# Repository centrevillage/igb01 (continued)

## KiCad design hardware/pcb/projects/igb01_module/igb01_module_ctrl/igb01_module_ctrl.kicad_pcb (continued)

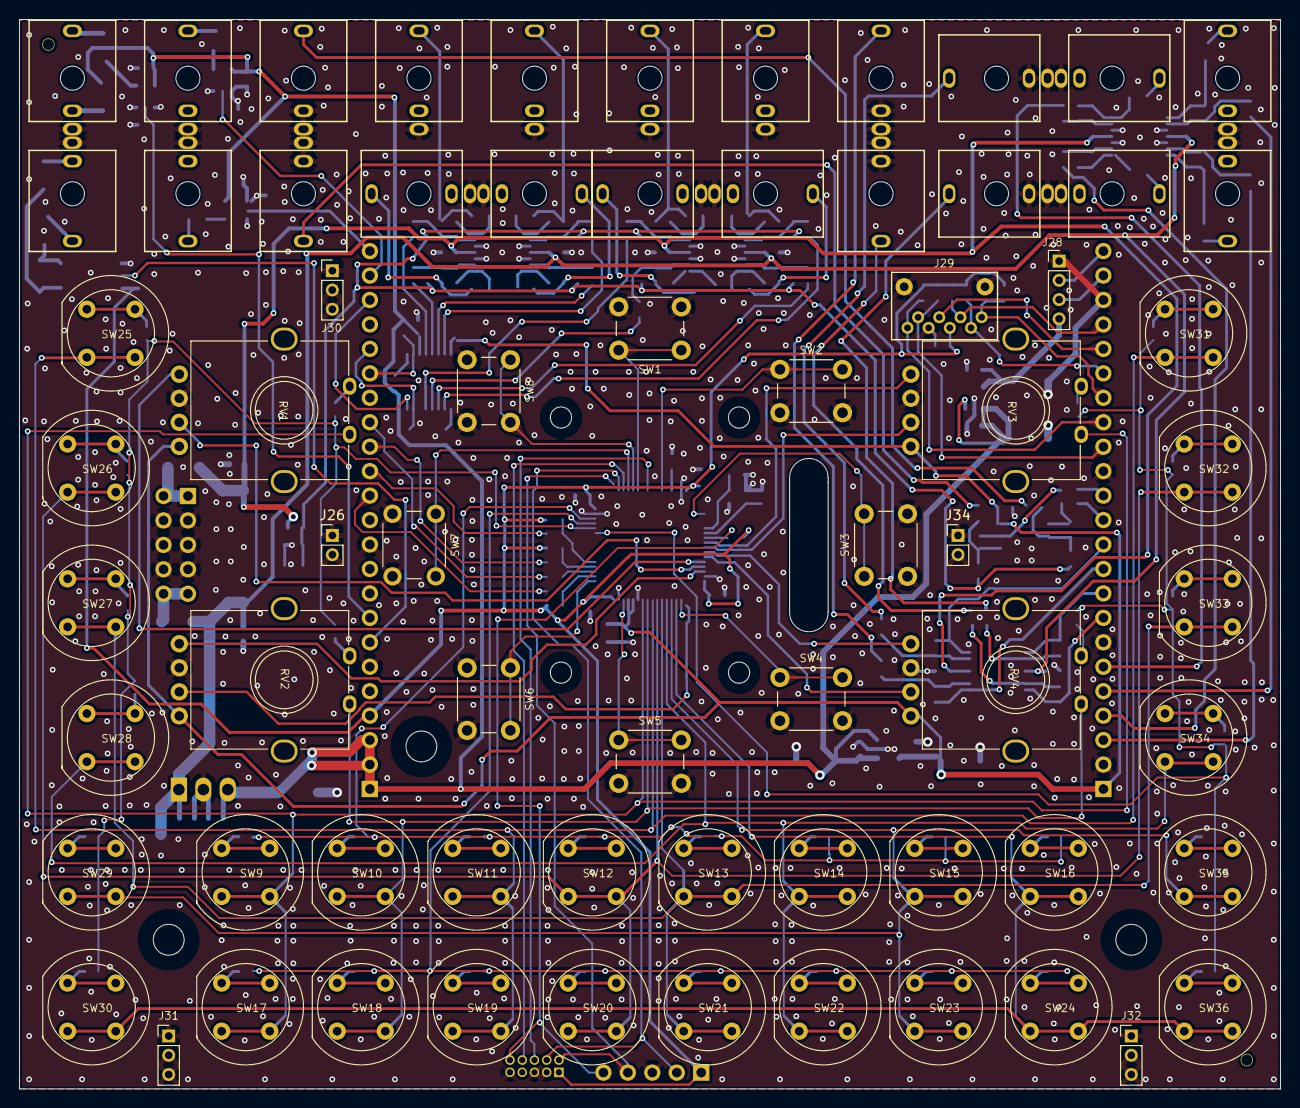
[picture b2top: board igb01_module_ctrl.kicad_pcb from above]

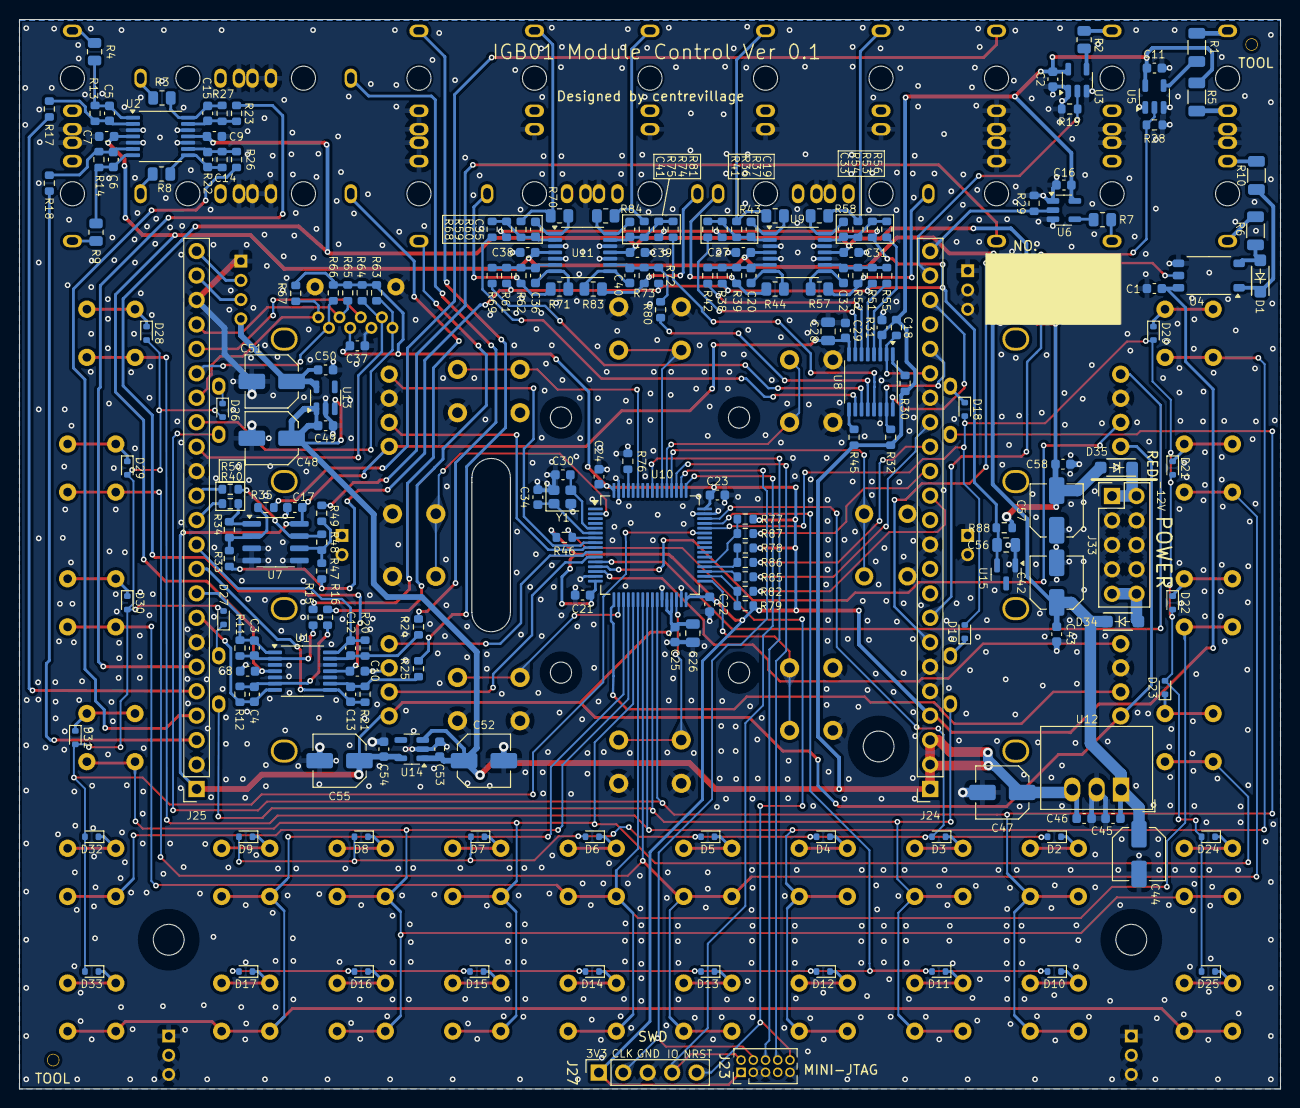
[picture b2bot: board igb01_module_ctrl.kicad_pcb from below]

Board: 2 copper layers, 131.0 x 111.1 mm, 278 parts (202 on the bottom side), 182 nets.

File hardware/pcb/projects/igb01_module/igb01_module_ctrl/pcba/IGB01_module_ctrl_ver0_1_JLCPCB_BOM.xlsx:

Comment | Designator | Footprint | LCSC Part #（optional）
220Ω,1206 | R1,R6,R5,R10 | R1206 | C17957
10kΩ,0603 | R20,R76,R77,R28,R19,R27,R12,R11,R21,R17,R46,R79,R78,R26,R29,R18 | R0603 | C25804
100kΩ,0603 | R24,R14,R16,R22,R23,R15,R25,R13 | R0603 | C25803
47Ω,0603 | R40,R50 | R0603 | C23182
200kΩ,0603 | R61,R72,R53,R49,R62,R54,R51,R59,R52,R33,R75,R36,R39,R37,R38,R74,R35,R73,R60,R47 | R0603 | C25811
47kΩ,0603 | R66,R63,R45,R32,R65,R31,R30,R67,R64 | R0603 | C25819
33kΩ,0603 | R69,R81,R80,R68,R34,R48,R56,R55,R41,R42 | R0603 | C4216
1kΩ,0805 | R70,R58,R4,R8,R84,R9,R43,R44,R2,R71,R83,R57,R7,R3 | R0805 | C17513
22Ω,0603 | R85,R82,R87,R86 | R0603 | C23345
3.3kΩ,0603 | R88 | R0603 | C22978
100nF,0603 | C11,C39,C53,C7,C1,C50,C38,C25,C23,C37,C54,C8,C29,C58,C49,C10,C24,C45,C17,C9,C27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 | R0603 | C14663
10pF,0603 | C14,C15,C5,C6 | R0603 | C1634
18pF,0603 | C20,C34,C3,C30,C33,C4,C19,C41,C13,C35,C12,C32,C40,C36 | R0603 | C1647
10uF,0805 | C26,C28 | C0805 | C15850
100uF,D5 | C51 | C_Elec_5x5.8 | C3347
1uF,0805 | C56 | C0805 | C28323
47uF,D5 | C57,C47,C55,C48,C44,C52,C42 | C_Elec_5x5.8 | C3337
1N4148,SOD-123 | D1 | SOD-123 | C81598
1N4148,SOD-523 | D23,D13,D8,D2,D14,D28,D16,D31,D6,D20,D15,D22,D5,D9,D29,D32,D25,D3,D24,D19,D30,D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 | SOD-523 | C27748
DSK34,SOD-123 | D35,D34 | SOD-123 | C41029
STM32G431RBT6 | U10 | LQFP-64_10x10mm_P0.5mm | C431633
TL074HIPWR,TSSOP | U11,U2,U1,U9 | TSSOP-14_4.4x5mm_P0.65mm | C4370424
R-78B5.0-2.0 | U12 | Converter_DCDC_RECOM_R-78B-2.0_THT | C5199920
LDK320-3.3V,SOT-23-5 | U14,U13 | SOT-23-5 | C136155
LM4040DBZ-10,SOT-23 | U15 | SOT-23 | C129969
TLP2361 | U4 | SO-5-6_4.55x3.7mm_P1.27mm | C107626
74AHCT1G125,SOT-23-5 | U5,U6,U3 | SOT-23-5 | C7484
MCP6002,SOIC | U7 | SOIC-8_3.9x4.9mm_P1.27mm | C7377
DAC8568IBPW,TSSOP | U8 | TSSOP-16_4.4x5mm_P0.65mm | C2680013
Crystal, 12MHz | Y1 | Crystal_SMD_2520-4Pin_2.5x2.0mm | C284156
Pin Header, 2x5, P1.27mm | J23 | PinHeader_2x05_P1.27mm_Vertical
Pin Socket, 1x23, P2.54mm | J24 | PinSocket_1x23_P2.54mm_Vertical
Pin Socket, 1x23, P2.54mm | J25 | PinSocket_1x23_P2.54mm_Vertical
Pin Socket, 1x5, P2.54mm | J27 | PinSocket_1x05_P2.54mm_Vertical
Pin Header, 2x5, P2.54mm | J33 | PinHeader_2x05_P2.54mm_Vertical

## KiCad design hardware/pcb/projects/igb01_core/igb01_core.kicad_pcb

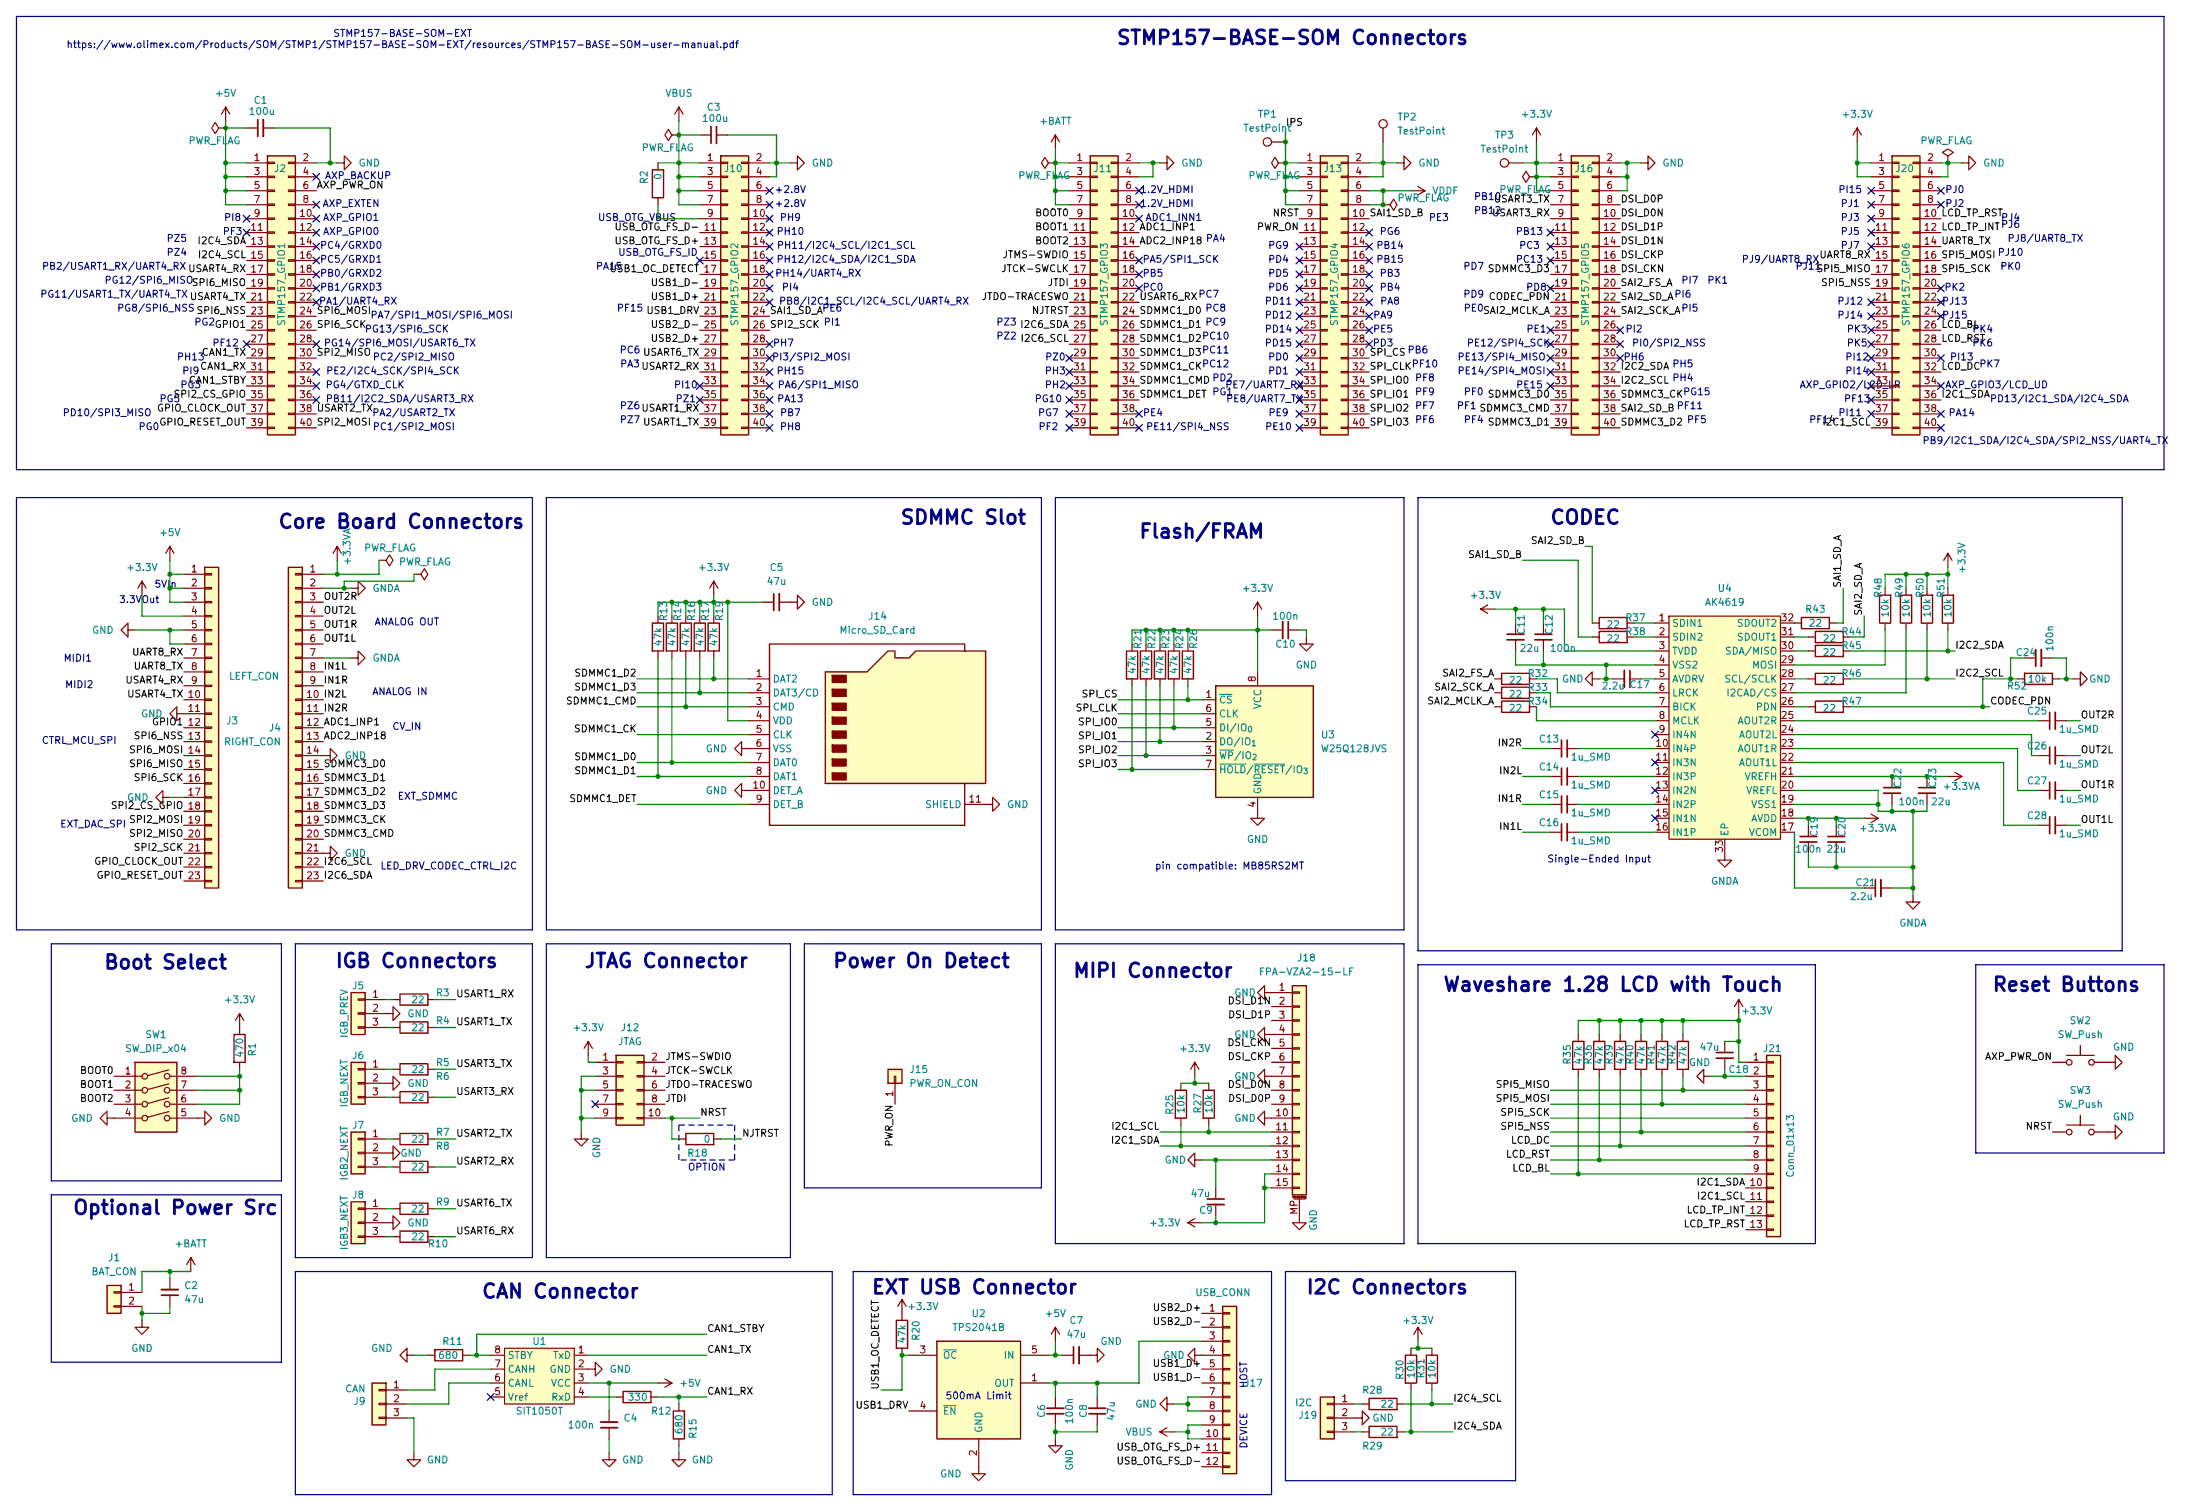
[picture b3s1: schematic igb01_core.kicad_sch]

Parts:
C1, C3: 100u; C_1206_3216Metric
C2, C5, C7, C8, C9, C18: 47u; C_0805_2012Metric
C4, C6, C10, C12, C19, C22, C24: 100n; C_0402_1005Metric
C11, C20, C23: 22u; C_0805_2012Metric
C13, C14, C15, C16, C25, C26, C27, C28: 1u_SMD; C_0805_2012Metric
C17, C21: 2.2u; C_0603_1608Metric
J1: BAT_CON; Molex_KK-254_AE-6410-02A_1x02_P2.54mm_Vertical
J2: STMP157_GPIO1; PinHeader_2x20_P1.27mm_Vertical_SMD
J3: LEFT_CON; PinHeader_1x23_P2.54mm_Vertical
J4: RIGHT_CON; PinHeader_1x23_P2.54mm_Vertical
J5: IGB_PREV; Molex_KK-254_AE-6410-03A_1x03_P2.54mm_Vertical
J6: IGB_NEXT; Molex_KK-254_AE-6410-03A_1x03_P2.54mm_Vertical
J7: IGB2_NEXT; Molex_KK-254_AE-6410-03A_1x03_P2.54mm_Vertical
J8: IGB3_NEXT; Molex_KK-254_AE-6410-03A_1x03_P2.54mm_Vertical
J9: CAN; Molex_KK-254_AE-6410-03A_1x03_P2.54mm_Vertical
J10: STMP157_GPIO2; PinHeader_2x20_P1.27mm_Vertical_SMD
J11: STMP157_GPIO3; PinHeader_2x20_P1.27mm_Vertical_SMD
J12: JTAG; PinHeader_2x05_P1.27mm_Vertical_SMD
J13: STMP157_GPIO4; PinHeader_2x20_P1.27mm_Vertical_SMD
J14: Micro_SD_Card; Molex_uSD_1040310811
J15: PWR_ON_CON; PinHeader_1x01_P2.54mm_Vertical
J16: STMP157_GPIO5; PinHeader_2x20_P1.27mm_Vertical_SMD
J17: USB_CONN; Molex_KK-254_AE-6410-12A_1x12_P2.54mm_Vertical
J18: FPA-VZA2-15-LF; Molex_200528-0150_1x15-1MP_P1.00mm_Horizontal
J19: I2C; Molex_KK-254_AE-6410-03A_1x03_P2.54mm_Vertical
J20: STMP157_GPIO6; PinHeader_2x20_P1.27mm_Vertical_SMD
J21: Conn_01x13; PinHeader_1x13_P2.54mm_Horizontal
R1: 470; R_0603_1608Metric
R2, R18: 0; R_0603_1608Metric
R3, R4, R5, R6, R7, R8, R9, R10, R28, R29: 22; R_0603_1608Metric
R11, R15: 680; R_0603_1608Metric
R12: 330; R_0603_1608Metric
R13, R14, R16, R17, R19, R20, R21, R22, R23, R24, R26, R35, R36, R39, R40, R41, R42: 47k; R_0402_1005Metric
R25, R27, R30, R31, R48, R49, R50, R51: 10k; R_0402_1005Metric
R32, R33, R34, R37, R38, R43, R44, R45, R46, R47: 22; R_0402_1005Metric
R52: 10k; R_0603_1608Metric
SW1: SW_DIP_x04; DIP_Switch_1.27mm_SMD
SW2, SW3: SW_Push; SW_SPST_PTS647_Sx38
TP1, TP2, TP3: TestPoint; PinHeader_1x01_P2.54mm_Vertical
U1: SIT1050T; SOP-8_3.9x4.9mm_P1.27mm
U2: TPS2041B; SOT-23-5
U3: W25Q128JVS; SOIC-8_5.3x5.3mm_P1.27mm
U4: AK4619; QFN-32-1EP_5x5mm_P0.5mm_EP3.6x3.6mm

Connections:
+3.3V: C5.1, C9.2, C10.2, C11.1, C12.1, C18.1, J3.4, J12.1, J14.4 (VDD), J16.1, J16.3, J16.5, J18.14, J18.15, J20.1, J20.3, J21.1, R1.1, R13.1, R14.1, R16.1, R17.1, R19.1, R20.1, R21.1, R22.1, R23.1, R24.1, R25.1, R26.1, R27.1, R30.1, R31.1, R35.1, R36.1, R39.1, R40.1, R41.1, R42.1, R48.2, R49.2, R50.2, R51.2, TP3.1, U3.8 (VCC), U4.3 (TVDD)
+3.3VA: C19.1, C20.1, C22.1, C23.1, J4.1, U4.18 (AVDD), U4.21 (VREFH)
+5V: C1.1, C4.2, C7.1, J2.1, J2.3, J2.5, J2.7, J3.1, J3.2, J3.3, U1.3 (VCC), U2.5 (IN)
+BATT: C2.2, J1.1, J11.1, J11.3, J11.5, J11.7
/ SAI1_SD_B: J13.10, R38.1
/ADC1_INP1: J4.12, J11.12
/ADC2_INP18: J4.13, J11.14
/AXP_PWR_ON: J2.6, SW2.1
/BOOT0: J11.9, SW1.1
/BOOT1: J11.11, SW1.2
/BOOT2: J11.13, SW1.3
/CAN1_RX: J2.31, R12.2, R15.2
/CAN1_STBY: J2.33, R11.1, U1.8 (STBY)
/CAN1_TX: J2.29, U1.1 (TxD)
/CODEC_PDN: C24.1, J16.21, R47.2, R52.2
/DSI_CKN: J16.18, J18.5
/DSI_CKP: J16.16, J18.6
/DSI_D0N: J16.10, J18.8
/DSI_D0P: J16.8, J18.9
/DSI_D1N: J16.14, J18.2
/DSI_D1P: J16.12, J18.3
/GPIO1: J2.25, J3.12
/GPIO_CLOCK_OUT: J2.37, J3.22
/GPIO_RESET_OUT: J2.39, J3.23
/I2C1_SCL: J18.11, J20.39, J21.11, R27.2
/I2C1_SDA: J18.12, J20.36, J21.10, R25.2
/I2C2_SCL: J16.34, R46.2, R50.1
/I2C2_SDA: J16.32, R45.2, R51.1
/I2C4_SCL: J2.15, R28.2, R31.2
/I2C4_SDA: J2.13, R29.2, R30.2
/I2C6_SCL: J4.22, J11.27
/I2C6_SDA: J4.23, J11.25
/IN1L: C16.1, J4.8
/IN1R: C15.1, J4.9
/IN2L: C14.1, J4.10
/IN2R: C13.1, J4.11
/IPS: J13.1, J13.3, J13.5, J13.7, TP1.1
/JTCK-SWCLK: J11.17, J12.4
/JTDI: J11.19, J12.8
/JTDO-TRACESWO: J11.21, J12.6
/JTMS-SWDIO: J11.15, J12.2
/LCD_BL: J20.26, J21.9, R35.2
/LCD_DC: J20.32, J21.7, R39.2
/LCD_RST: J20.28, J21.8, R36.2
/LCD_TP_INT: J20.12, J21.12
/LCD_TP_RST: J20.10, J21.13
/NJTRST: J11.23, R18.2
/NRST: J12.10, J13.9, R18.1, SW3.1
/OUT1L: C28.2, J4.6
/OUT1R: C27.2, J4.5
/OUT2L: C26.2, J4.4
/OUT2R: C25.2, J4.3
/PWR_ON: J13.11, J15.1
/SAI1_SD_A: J10.24, R43.2
/SAI2_FS_A: J16.20, R32.1
/SAI2_MCLK_A: J16.23, R34.1
/SAI2_SCK_A: J16.24, R33.1
/SAI2_SD_A: J16.22, R44.2
/SAI2_SD_B: J16.38, R37.1
/SDMMC1_CK: J11.32, J14.5 (CLK)
/SDMMC1_CMD: J11.34, J14.3 (CMD), R16.2
/SDMMC1_D0: J11.24, J14.7 (DAT0), R14.2
/SDMMC1_D1: J11.26, J14.8 (DAT1), R13.2
/SDMMC1_D2: J11.28, J14.1 (DAT2), R19.2
/SDMMC1_D3: J11.30, J14.2 (DAT3/CD), R17.2
/SDMMC1_DET: J11.36, J14.9 (DET_B)
/SDMMC3_CK: J4.19, J16.36
/SDMMC3_CMD: J4.20, J16.37
/SDMMC3_D0: J4.15, J16.35
/SDMMC3_D1: J4.16, J16.39
/SDMMC3_D2: J4.17, J16.40
/SDMMC3_D3: J4.18, J16.17
/SPI2_CS_GPIO: J2.35, J3.18
/SPI2_MISO: J2.30, J3.20
/SPI2_MOSI: J2.40, J3.19
/SPI2_SCK: J3.21, J10.26
/SPI5_MISO: J20.17, J21.3, R42.2
/SPI5_MOSI: J20.16, J21.4, R41.2
/SPI5_NSS: J20.19, J21.6, R40.2
/SPI5_SCK: J20.18, J21.5
/SPI6_MISO: J2.19, J3.15
/SPI6_MOSI: J2.24, J3.14
/SPI6_NSS: J2.23, J3.13
/SPI6_SCK: J2.26, J3.16
/SPI_CLK: J13.32, U3.6 (CLK)
/SPI_CS: J13.30, R26.2, U3.1 (~CS)
/SPI_IO0: J13.34, R24.2, U3.5 (DI/IO_{0})
/SPI_IO1: J13.36, R23.2, U3.2 (DO/IO_{1})
/SPI_IO2: J13.38, R22.2, U3.3 (~WP/IO_{2})
/SPI_IO3: J13.40, R21.2, U3.7 (~HOLD/~RESET/IO_{3})
/UART8_RX: J3.7, J20.15
/UART8_TX: J3.8, J20.14
/USART1_RX: J10.37, R3.2
/USART1_TX: J10.39, R4.2
/USART2_RX: J10.31, R8.2
/USART2_TX: J2.38, R7.2
/USART3_RX: J16.9, R6.2
/USART3_TX: J16.7, R5.2
/USART4_RX: J2.17, J3.9
/USART4_TX: J2.21, J3.10
/USART6_RX: J11.22, R10.2
/USART6_TX: J10.29, R9.2
/USB1_D+: J10.21, J17.5
/USB1_D-: J10.19, J17.6
/USB1_DRV: J10.23, U2.4 (~EN)
/USB1_OC_DETECT: J10.17, R20.2, U2.3 (~OC)
/USB2_D+: J10.27, J17.1
/USB2_D-: J10.25, J17.2
/USB_OTG_FS_D+: J10.13, J17.11
/USB_OTG_FS_D-: J10.11, J17.12
GND: C1.2, C2.1, C3.2, C4.1, C5.2, C6.1, C7.2, C8.1, C9.1, C10.1, C11.2, C12.2, C17.2, C18.2, C24.2, J1.2, J2.2, J3.5, J3.6, J3.11, J3.17, J4.14, J4.21, J5.2, J6.2, J7.2, J8.2, J9.3, J10.2, J10.4, J11.2, J11.4, J12.3, J12.5, J12.9, J13.2, J13.4, J14.6 (VSS), J14.10 (DET_A), J14.11 (SHIELD), J16.2, J16.4, J16.6, J17.4, J17.7, J17.8, J18.1, J18.4, J18.7, J18.10, J18.13, J18.MP (MountPin), J19.2, J20.2, J20.4, J21.2, R11.2, R15.1, R52.1, SW1.4, SW1.5, SW2.2, SW3.2, TP2.1, U1.2 (GND), U2.2 (GND), U3.4 (GND), U4.4 (VSS2)
GNDA: C19.2, C20.2, C21.2, C22.2, C23.2, J4.2, J4.7, U4.19 (VSS1), U4.20 (VREFL), U4.33 (EP)
unnamed: J5.1, R3.1
unnamed: J5.3, R4.1
unnamed: J6.1, R5.1
unnamed: J6.3, R6.1
unnamed: J7.1, R7.1
unnamed: J7.3, R8.1
unnamed: J8.1, R9.1
unnamed: J8.3, R10.1
unnamed: J9.1, U1.7 (CANH)
unnamed: J9.2, U1.6 (CANL)
unnamed: J10.9, R2.1
unnamed: C6.2, C8.2, J17.3, U2.1 (OUT)
unnamed: J19.1, R28.1
unnamed: J19.3, R29.1
unnamed: R1.2, SW1.6, SW1.7, SW1.8
unnamed: R12.1, U1.4 (RxD)
unnamed: C28.1, U4.22 (AOUT1L)
unnamed: C27.1, U4.23 (AOUT1R)
unnamed: C26.1, U4.24 (AOUT2L)
unnamed: C25.1, U4.25 (AOUT2R)
unnamed: C17.1, U4.5 (AVDRV)
unnamed: R33.2, U4.7 (BICK)
unnamed: R49.1, U4.27 (I2CAD/CS)
unnamed: C16.2, U4.16 (IN1P)
unnamed: C15.2, U4.14 (IN2P)
unnamed: C14.2, U4.12 (IN3P)
unnamed: C13.2, U4.10 (IN4P)
unnamed: R32.2, U4.6 (LRCK)
unnamed: R34.2, U4.8 (MCLK)
unnamed: R48.1, U4.29 (MOSI)
unnamed: R47.1, U4.26 (PDN)
unnamed: R46.1, U4.28 (SCL/SCLK)
unnamed: R45.1, U4.30 (SDA/MISO)
unnamed: R37.2, U4.1 (SDIN1)
unnamed: R38.2, U4.2 (SDIN2)
unnamed: R44.1, U4.31 (SDOUT1)
unnamed: R43.1, U4.32 (SDOUT2)
unnamed: C21.1, U4.17 (VCOM)
VBUS: C3.1, J10.1, J10.3, J10.5, J10.7, J17.9, J17.10, R2.2
VDDF: J13.6, J13.8

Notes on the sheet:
PG4/GTXD_CLK
PD7
STMP157-BASE-SOM-EXT https://www.olimex.com/Products/SOM/STMP1/STMP157-BASE-SOM-EXT/resources/STMP157-BASE-SOM-user-manual.pdf
PF15
PK5
PH14/UART4_RX
PB14
PG8/SPI6_NSS
PD4
PE1
PZ4
PD8
PF10
PK4
PA14
PE5
PI11
Single-Ended Input
PC3
PE10
Boot Select
PK3
PI12
3.3VOut
PF2
Reset Buttons
PH5
PG2
CV_IN
PB11/I2C2_SDA/USART3_RX
PJ3
JTAG Connector
+2.8V
PG9
PH13
500mA Limit
Optional Power Src
PI6
PD14
LED_DRV_CODEC_CTRL_I2C

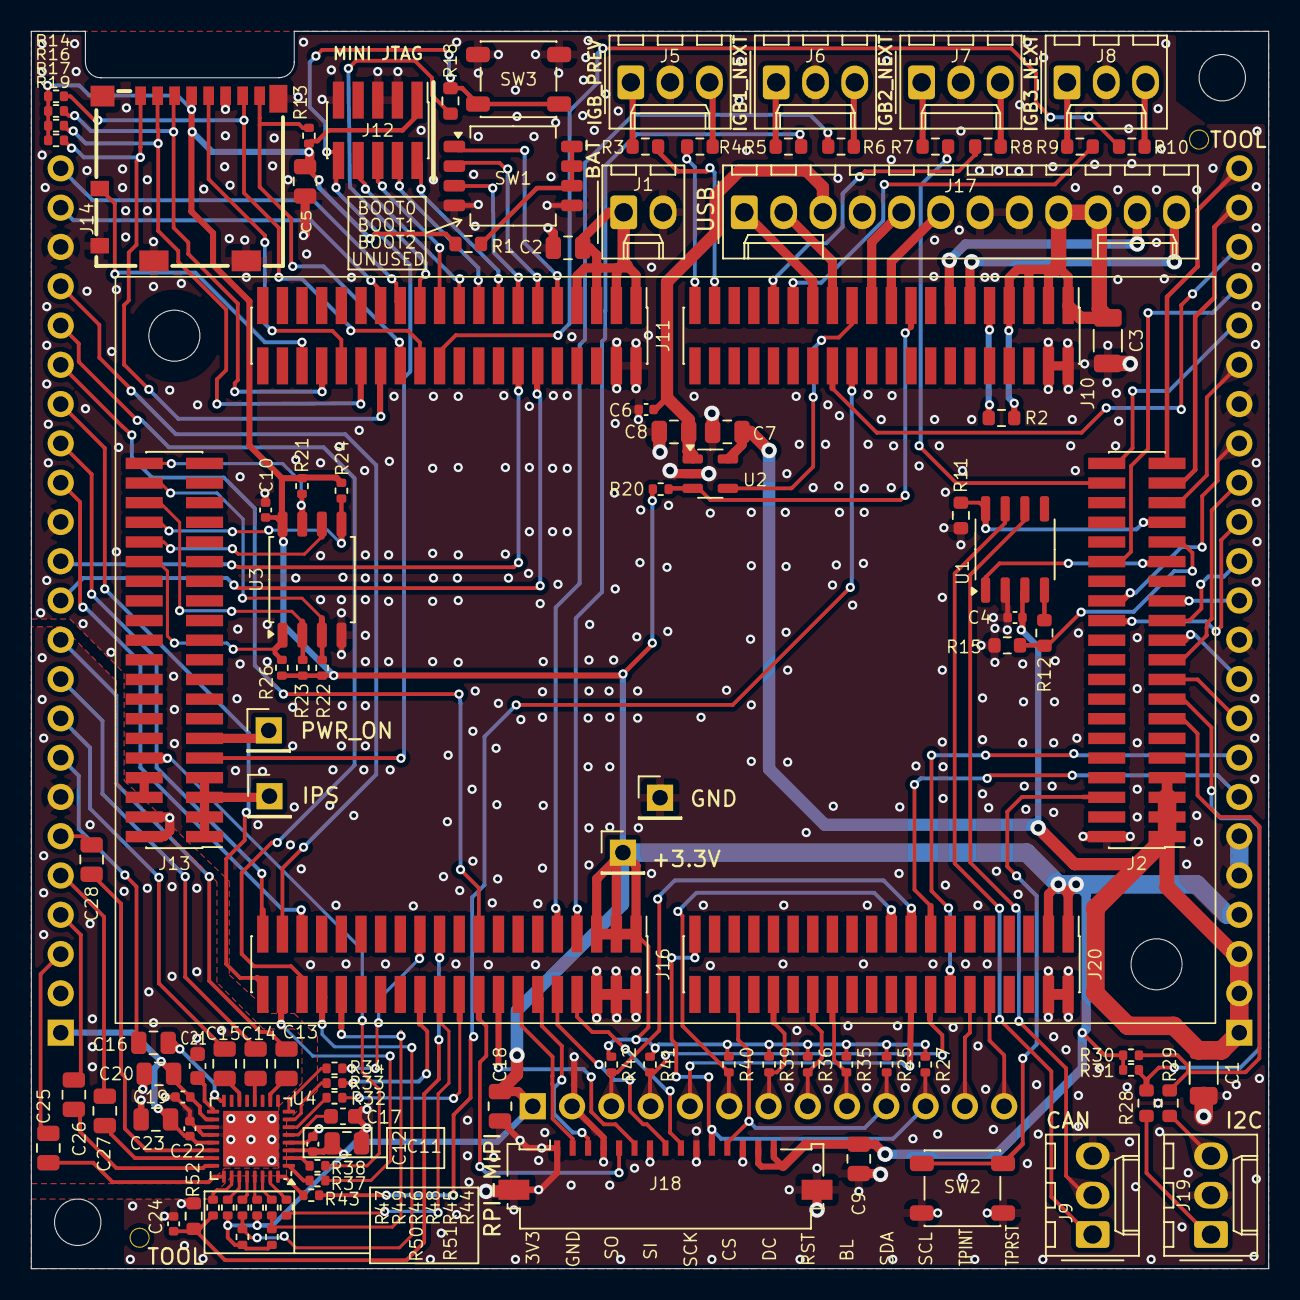
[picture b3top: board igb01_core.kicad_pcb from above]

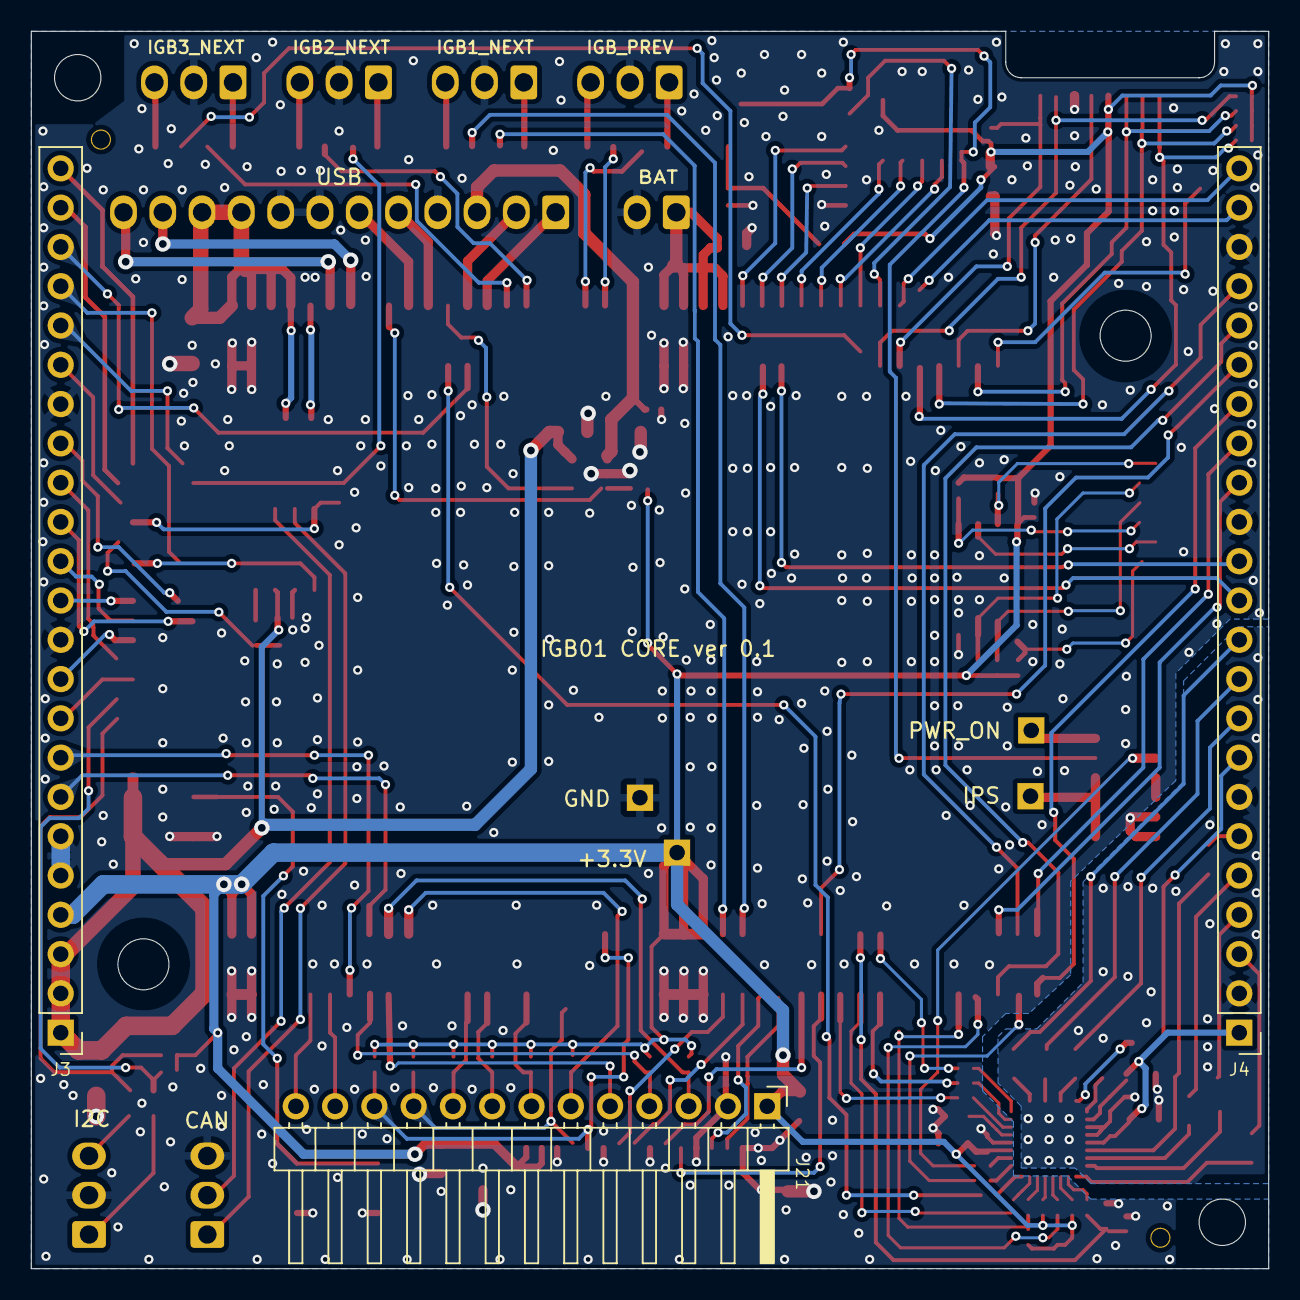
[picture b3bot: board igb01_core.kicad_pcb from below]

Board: 2 copper layers, 80.0 x 80.0 mm, 111 parts (3 on the bottom side), 152 nets.

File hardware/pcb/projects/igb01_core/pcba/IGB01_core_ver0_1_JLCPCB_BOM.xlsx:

Comment | Designator | Footprint | LCSC Part #（optional）
22uF | C11,C23,C20 | C0805 | C45783
2.2uF | C17,C21 | C0603 | C23630
1uF | C25,C14,C27,C15,C28,C16,C13,C26 | C0805 | C1712
100uF | C3,C1 | C1206 | C15008
100nF | C4,C10,C12,C22,C24,C19,C6 | C0402 | C1525
47uF | C8,C9,C5,C2,C7,C18 | C0805 | C16780
470Ω | R1 | R0603 | C23179
680Ω | R11,R15 | R0603 | C23228
330Ω | R12 | R0603 | C23138
0Ω | R2,R18 | R0603 | C21189
22Ω | R32,R44,R47,R34,R37,R45,R43,R33,R38,R46 | R0402 | C25092
47kΩ | R39,R20,R16,R36,R17,R14,R40,R23,R22,R21,R13,R35,R42,R19,R24,R41,R26 | R0402 | C25792
22Ω | R5,R6,R10,R28,R4,R3,R29,R9,R8,R7 | R0603 | C23345
10kΩ | R50,R51,R48,R31,R49,R30,R25,R27 | R0402 | C25744
10kΩ | R52 | R0603 | C25804
SIT1050T | U1 | SOP-8_3.9x4.9mm_P1.27mm | C313021
TPS2041B | U2 | SOT-23-5 | C51386
W25Q128JVS | U3 | SOIC-8_5.3x5.3mm_P1.27mm | C97521
AK4619 | U4 | QFN-32-1EP_5x5mm_P0.5mm_EP3.6x3.6mm | C3034747
DIP Switch, SMD | SW1 | DIP_Switch_1.27mm_SMD | C40736
Push Switch | SW3,SW2 | SW_SPST_PTS647_Sx38 | C2689502
Molex KK-254, 2 pin | J1 | Molex_KK-254_AE-6410-02A_1x02_P2.54mm_Vertical
Pin Header 2x20,pitch1.27mm,SMD | J10 | PinHeader_2x20_P1.27mm_Vertical_SMD | C2881925
Pin Header 2x20,pitch1.27mm,SMD | J11 | PinHeader_2x20_P1.27mm_Vertical_SMD | C2881925
Pin Header 2x05,pitch1.27mm,SMD | J12 | PinHeader_2x05_P1.27mm_Vertical_SMD | C41376037
Pin Header 2x20,pitch1.27mm,SMD | J13 | PinHeader_2x20_P1.27mm_Vertical_SMD | C2881925
Molex uSD 1040310811 | J14 | Molex_uSD_1040310811 | C585350
Pin Header 2x20,pitch1.27mm,SMD | J16 | PinHeader_2x20_P1.27mm_Vertical_SMD | C2881925
Molex KK-254, 12 pin | J17 | Molex_KK-254_AE-6410-12A_1x12_P2.54mm_Vertical
Molex 200528-0150 | J18 | Molex_200528-0150_1x15-1MP_P1.00mm_Horizontal | C6050043
Molex KK-254, 3 pin | J19 | Molex_KK-254_AE-6410-03A_1x03_P2.54mm_Vertical
Pin Header 2x20,pitch1.27mm,SMD | J2 | PinHeader_2x20_P1.27mm_Vertical_SMD | C2881925
Pin Header 2x20,pitch1.27mm,SMD | J20 | PinHeader_2x20_P1.27mm_Vertical_SMD | C2881925
Pin Header 1x13,pitch2.54mm,horizontal | J21 | PinHeader_1x13_P2.54mm_Horizontal
Pin Header 1x23,pitch2.54mm,vertical | J3 | PinHeader_1x23_P2.54mm_Vertical
Pin Header 1x23,pitch2.54mm,vertical | J4 | PinHeader_1x23_P2.54mm_Vertical
Molex KK-254, 3 pin | J5 | Molex_KK-254_AE-6410-03A_1x03_P2.54mm_Vertical
Molex KK-254, 3 pin | J6 | Molex_KK-254_AE-6410-03A_1x03_P2.54mm_Vertical
Molex KK-254, 3 pin | J7 | Molex_KK-254_AE-6410-03A_1x03_P2.54mm_Vertical
Molex KK-254, 3 pin | J8 | Molex_KK-254_AE-6410-03A_1x03_P2.54mm_Vertical
Molex KK-254, 3 pin | J9 | Molex_KK-254_AE-6410-03A_1x03_P2.54mm_Vertical

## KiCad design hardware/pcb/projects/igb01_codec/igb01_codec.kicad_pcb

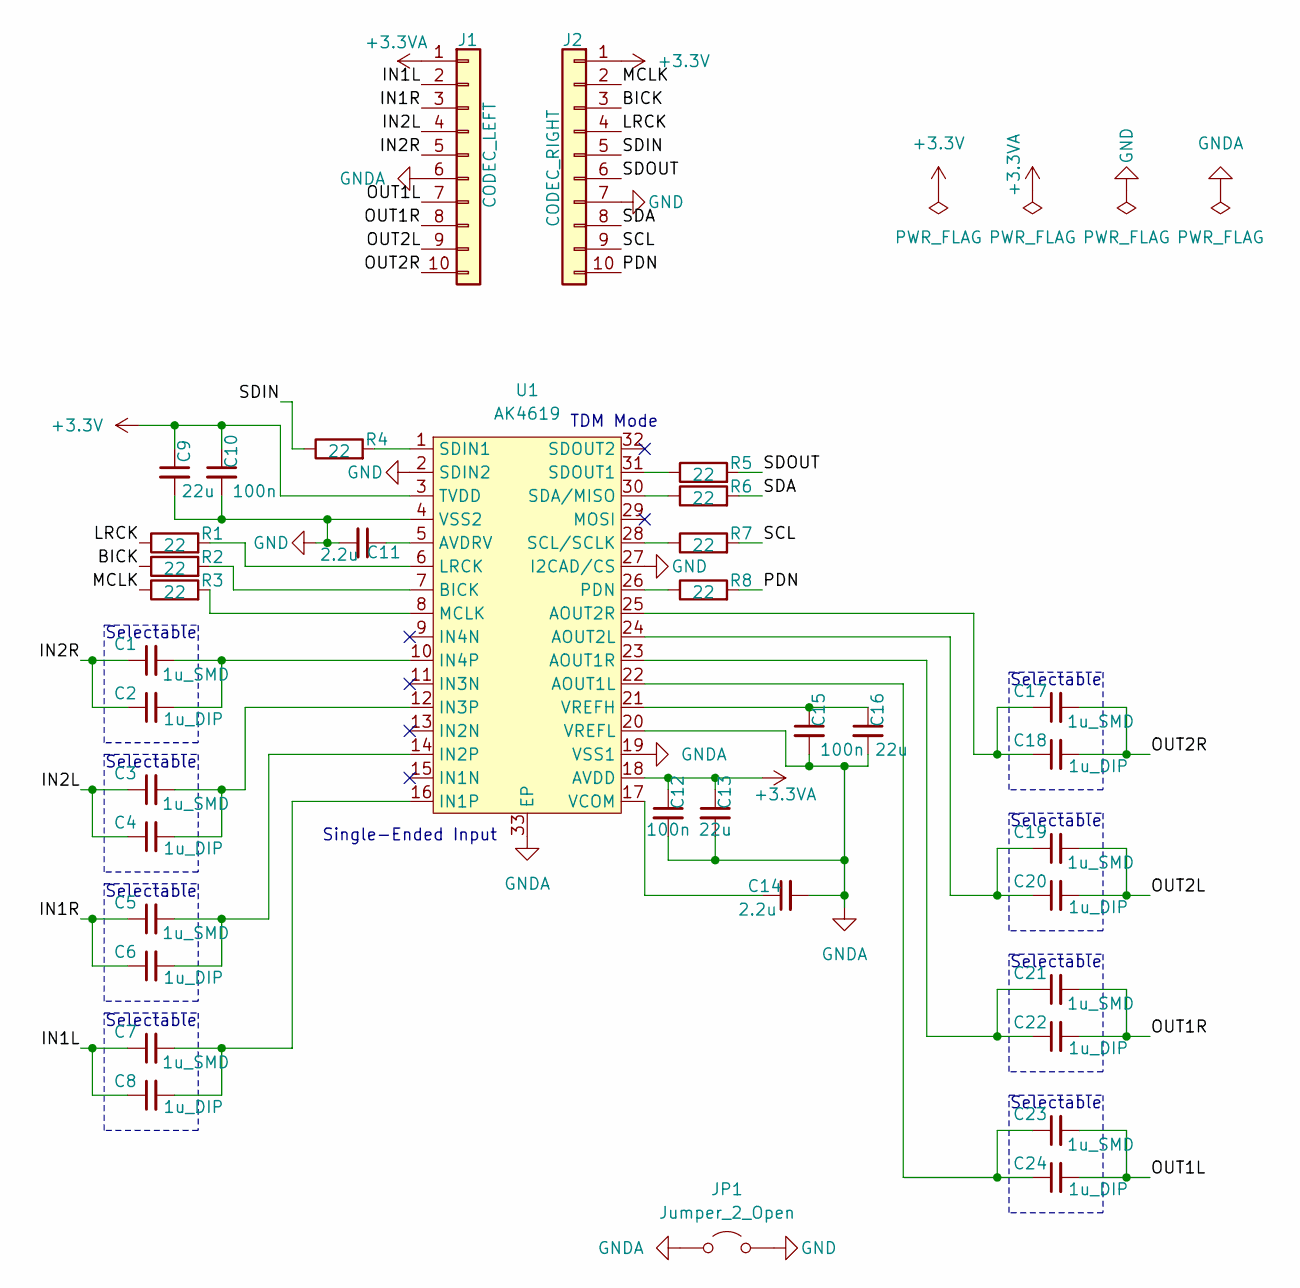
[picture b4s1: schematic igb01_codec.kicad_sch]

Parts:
C1, C3, C5, C7, C17, C19, C21, C23: 1u_SMD; C_1206_3216Metric
C2, C4, C6, C8, C18, C20, C22, C24: 1u_DIP; C_Rect_L7.2mm_W4.5mm_P5.00mm_FKS2_FKP2_MKS2_MKP2
C9, C13, C16: 22u; C_0805_2012Metric
C10, C12, C15: 100n; C_0402_1005Metric
C11, C14: 2.2u; C_0603_1608Metric
J1: CODEC_LEFT; PinHeader_1x10_P2.54mm_Vertical
J2: CODEC_RIGHT; PinHeader_1x10_P2.54mm_Vertical
JP1: Jumper_2_Open; SolderJumper-2_P1.3mm_Open_RoundedPad1.0x1.5mm
R1, R2, R3, R4, R5, R6, R7, R8: 22; R_0402_1005Metric
U1: AK4619; QFN-32-1EP_5x5mm_P0.5mm_EP3.6x3.6mm

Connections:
+3.3V: C9.1, C10.1, J2.1, U1.3 (TVDD)
+3.3VA: C12.1, C13.1, J1.1, U1.18 (AVDD)
/BICK: J2.3, R2.1
/IN1L: C7.1, C8.1, J1.2
/IN1R: C5.1, C6.1, J1.3
/IN2L: C3.1, C4.1, J1.4
/IN2R: C1.1, C2.1, J1.5
/LRCK: J2.4, R1.1
/MCLK: J2.2, R3.1
/OUT1L: C23.2, C24.2, J1.7
/OUT1R: C21.2, C22.2, J1.8
/OUT2L: C19.2, C20.2, J1.9
/OUT2R: C17.2, C18.2, J1.10
/PDN: J2.10, R8.2
/SCL: J2.9, R7.2
/SDA: J2.8, R6.2
/SDIN: J2.5, R4.1
/SDOUT: J2.6, R5.2
GND: C9.2, C10.2, C11.2, J2.7, JP1.2 (B), U1.2 (SDIN2), U1.4 (VSS2), U1.27 (I2CAD/CS)
GNDA: C12.2, C13.2, C14.2, C15.2, C16.2, J1.6, JP1.1 (A), U1.19 (VSS1), U1.20 (VREFL), U1.33 (EP)
unnamed: C23.1, C24.1, U1.22 (AOUT1L)
unnamed: C21.1, C22.1, U1.23 (AOUT1R)
unnamed: C19.1, C20.1, U1.24 (AOUT2L)
unnamed: C17.1, C18.1, U1.25 (AOUT2R)
unnamed: C11.1, U1.5 (AVDRV)
unnamed: R2.2, U1.7 (BICK)
unnamed: C7.2, C8.2, U1.16 (IN1P)
unnamed: C5.2, C6.2, U1.14 (IN2P)
unnamed: C3.2, C4.2, U1.12 (IN3P)
unnamed: C1.2, C2.2, U1.10 (IN4P)
unnamed: R1.2, U1.6 (LRCK)
unnamed: R3.2, U1.8 (MCLK)
unnamed: R8.1, U1.26 (PDN)
unnamed: R7.1, U1.28 (SCL/SCLK)
unnamed: R6.1, U1.30 (SDA/MISO)
unnamed: R4.2, U1.1 (SDIN1)
unnamed: R5.1, U1.31 (SDOUT1)
unnamed: C14.1, U1.17 (VCOM)
unnamed: C15.1, C16.1, U1.21 (VREFH)

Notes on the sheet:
Selectable
Single-Ended Input
TDM Mode

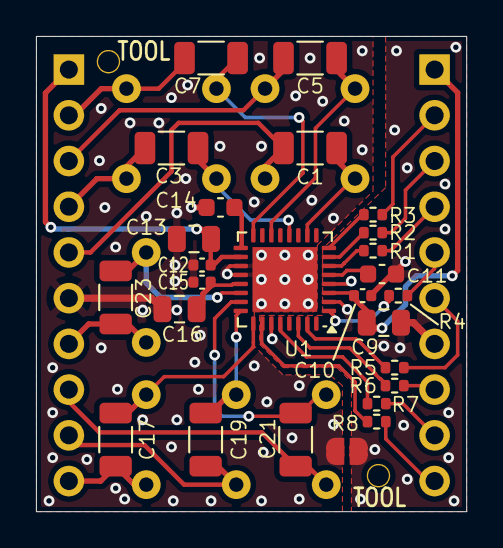
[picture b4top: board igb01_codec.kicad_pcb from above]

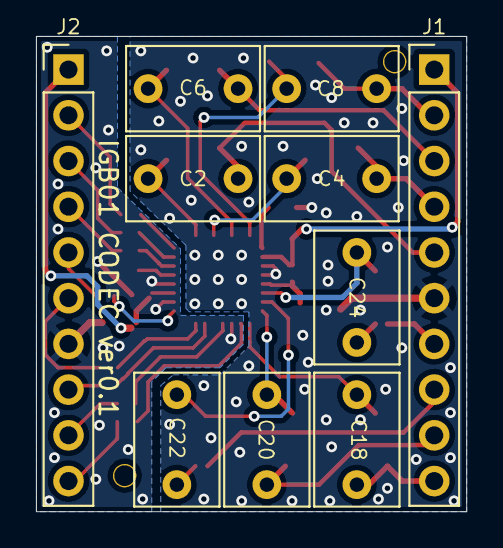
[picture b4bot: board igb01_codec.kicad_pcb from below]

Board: 2 copper layers, 23.9 x 26.4 mm, 36 parts (10 on the bottom side), 39 nets.

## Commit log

2025-01-19 add core board schematic
2025-01-20 add Config pins & Ext GPIO pins
2025-01-20 add AK4619 symbol
2025-01-21 add CODEC_PDN pin & 3.3V Out pin
2025-01-21 add codec board schematic
2025-01-22 add LDC connectors on the core board
2025-02-05 add control pcb schematic
2025-02-18 update igb01 control board schematic
2025-12-14 update led board
2025-12-16 update igb01 led pcb
2025-12-17 update igb01 control schematic
2025-12-18 update led schematic
2025-12-24 update led&control schematics
2025-12-25 update codec sch&pcb
2025-12-26 update core board
2025-12-28 update core board sch&pcb
2025-12-29 add CAN connector to core board
2025-12-29 change header pin assignment for core board
2025-12-31 connect all pads for core pcb
2025-12-31 core pcb ver0.1
2026-01-09 add igb01_module
2026-01-09 update igb01 module control board
2026-01-19 update igb01 module control board: layout all nets
2026-01-20 igb01 module control board ver 0.1
2026-01-26 add igb01 module led board
2026-01-28 add igb01 module panel pcb
2026-01-30 update igb01 core board & create gerber files
2026-02-03 add igb01 core board BOM&CPL file
2026-02-19 add production file for igb01 module ctrl board
2026-02-19 add production files for igb01 module led
2026-02-19 add gerber files for igb01 module panel
2026-03-05 change sd/mmc card hole size
2026-04-25 add submodule (stm32mp1-baremetal)
2026-04-25 add schematic pdfs
2026-04-25 add igb_sdk
